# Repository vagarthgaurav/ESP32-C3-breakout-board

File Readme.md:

# ESP32-C3 breakout board

A simple breakout board for the ESP32-C3 Microcontroller.
It uses a chip antenna for wifi and bluetooth.
It has an RGB LED on pin 10.

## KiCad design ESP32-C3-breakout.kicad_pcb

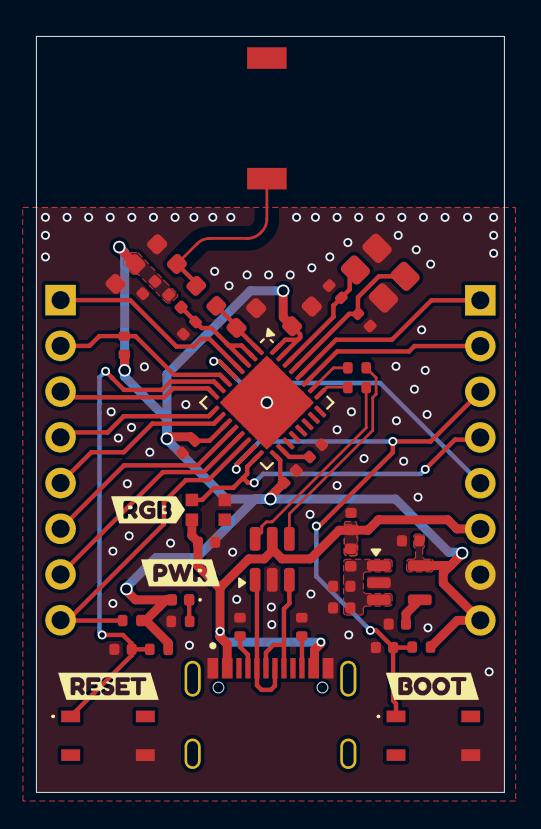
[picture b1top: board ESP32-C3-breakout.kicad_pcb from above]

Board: 4 copper layers, 26.0 x 42.0 mm, 47 parts (0 on the bottom side), 34 nets.

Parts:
ANT1: 2450AT43A100E; ANTC7020X130N
C1, C2: 20p; C_0402_1005Metric
C3, C4, C7, C8, C10, C12, C13, C14, C17, C20: 100n; C_0402_1005Metric
C6, C9: 10u; C_0603_1608Metric
C11: 1uF; C_0402_1005Metric
C15, C16: 10u; C_0402_1005Metric
C18: 3p3; C_0603_1608Metric
C19: 2.7; C_0603_1608Metric
D1: PWR_LED; LED_0402_1005Metric
D2: WS2812B-2020; LED_WS2812B-2020_PLCC4_2.0x2.0mm
J1: TYPE-C-31-M-12; HRO_TYPE-C-31-M-12
J2: Pins_left; PinHeader_1x08_P2.54mm_Vertical
J3: Pins_right; PinHeader_1x08_P2.54mm_Vertical
L1, L2: 2n2; L_0402_1005Metric
L3: 2n4; L_0603_1608Metric
R1, R2, R3, R4, R7, R8: 5k1; R_0402_1005Metric
R5, R6: 22R; R_0402_1005Metric
R9: 110R; R_0402_1005Metric
S1: SKRPARE010
S2: SKRPACE010; SKRPARE010
U1: ESP32-C3FH4X; QFN-32-1EP_5x5mm_P0.5mm_EP3.7x3.7mm
U2: USBLC6-2SC6; SOT-23-6
U3: SPX3819M5-L-3-3; SOT-23-5
Y1: 40Mhz; Crystal_SMD_3225-4Pin_3.2x2.5mm
kibuzzard-68B18F2D: G***; kibuzzard-68B18F2D
kibuzzard-68B18F76: G***; kibuzzard-68B18F76
kibuzzard-68B1700C: G***; kibuzzard-68B1700C
kibuzzard-68B19021: G***; kibuzzard-68B19021

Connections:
+3V3: C3.1, C4.1, C6.1, C8.1, C9.1, C16.1, D1.2 (A), J3.8, L1.1, R1.1, R4.1, R7.1, R8.1, U1.11 (VDD3P3_RTC), U1.17 (VDD3P3_CPU), U1.31 (VDDA), U1.32 (VDDA), U3.5 (OUT)
/CHIP_EN: C10.1, R1.2, S1.1, U1.7 (CHIP_EN)
/GPIO0: J3.5, U1.5 (XTAL_32K_N)
/GPIO1: J2.1, U1.4 (XTAL_32K_P)
/GPIO2: J2.2, R7.2, U1.6 (GPIO2)
/GPIO3: J2.3, U1.8 (GPIO3)
/GPIO4: J2.4, U1.9 (MTMS)
/GPIO5: J2.5, U1.10 (MTDI)
/GPIO6: J2.6, U1.12 (MTCK)
/GPIO7: J2.7, U1.13 (MTDO)
/GPIO8: J2.8, R8.2, U1.14 (GPIO8)
/GPIO9_BOOT: C12.1, J3.3, R4.2, S2.1, U1.15 (GPIO9)
/GPIO10_RGB_LED: D2.3 (DIN), J3.4, U1.16 (GPIO10)
/GPIO21_UART_RX: J3.2, U1.27 (U0RXD)
/GPIO21_UART_TX: J3.1, U1.28 (U0TXD)
/LDO_BP: C17.1, U3.4 (BP)
/LDO_IN: C14.1, C15.1, L2.2, U3.1 (IN), U3.3 (EN)
/RF: C18.1, L3.1, U1.1 (LNA_IN)
/RF_ANT: ANT1.1 (FEED), C19.1, L3.2
/USBC_CC1: J1.A5 (CC1), R2.1
/USBC_CC2: J1.B5 (CC2), R3.1
/USBC_N: J1.A7 (D-), J1.B7 (D-), U2.1 (I/O1)
/USBC_P: J1.A6 (D+), J1.B6 (D+), U2.3 (I/O2)
/USB_N: R5.1, U2.6 (I/O1)
/USB_P: R6.1, U2.4 (I/O2)
/USBu_N: R5.2, U1.25 (GPIO18)
/USBu_P: R6.2, U1.26 (GPIO19)
/VDDA_3V3: C7.1, L1.2, U1.2 (VDD3P3), U1.3 (VDD3P3)
/VDD_SPI: C11.1, U1.18 (VDD_SPI)
/XTAL_N: C1.1, U1.29 (XTAL_N), Y1.1
/XTAL_P: C2.1, U1.30 (XTAL_P), Y1.3
GND: C1.2, C2.2, C3.2, C4.2, C6.2, C7.2, C8.2, C9.2, C10.2, C11.2, C12.2, C13.2, C14.2, C15.2, C16.2, C17.2, C18.2, C19.2, C20.2, D2.2 (VSS), J1.A1 (GND), J1.B1 (GND), J3.7, R2.2, R3.2, R9.1, S1.4, S2.4, U1.33 (GND), U2.2 (GND), U3.2 (GND), Y1.2, Y1.4
unnamed: D1.1 (K), R9.2
VBUS: C13.1, C20.1, D2.4 (VDD), J1.A4 (VBUS), J1.B4 (VBUS), J3.6, L2.1, U2.5 (VBUS)

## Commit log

2026-01-05 doc: Add images and schematic pdf
